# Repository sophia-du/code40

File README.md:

# code40
Pro-Micro compatible 40% ortholinear keyboard
- [Case Specifications](https://github.com/sophia-du/code40/blob/main/case/README.md)
- [PCB Specifications](https://github.com/sophia-du/code40/blob/main/pcb/README.md)
- [Firmware](https://github.com/sophia-du/code40/blob/main/qmk/README.md)
#

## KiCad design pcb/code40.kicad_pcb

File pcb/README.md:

# PCB Specifications
- Dimensions: 229 x 105 x 1.6 mm
- 2 layers, 1.6 mm thick, 1 oz copper
## Hardware
| Component | Amount |
|-----------|--------|
| Pro-Micro Compatible Microcontroller w/ Headers| 1 |
| 6 x 6 mm Push Button | 1 |
| 100 Ω Through-Hole Resistors | 2 |
| 5 mm Through-Hole LEDs | 2 |
| 1N4148 Diodes | 47 |
| Cherry MX Compatible Switches | 47 |
| 2u PCB Mounted Stabilizers | 1 |
## Assembly

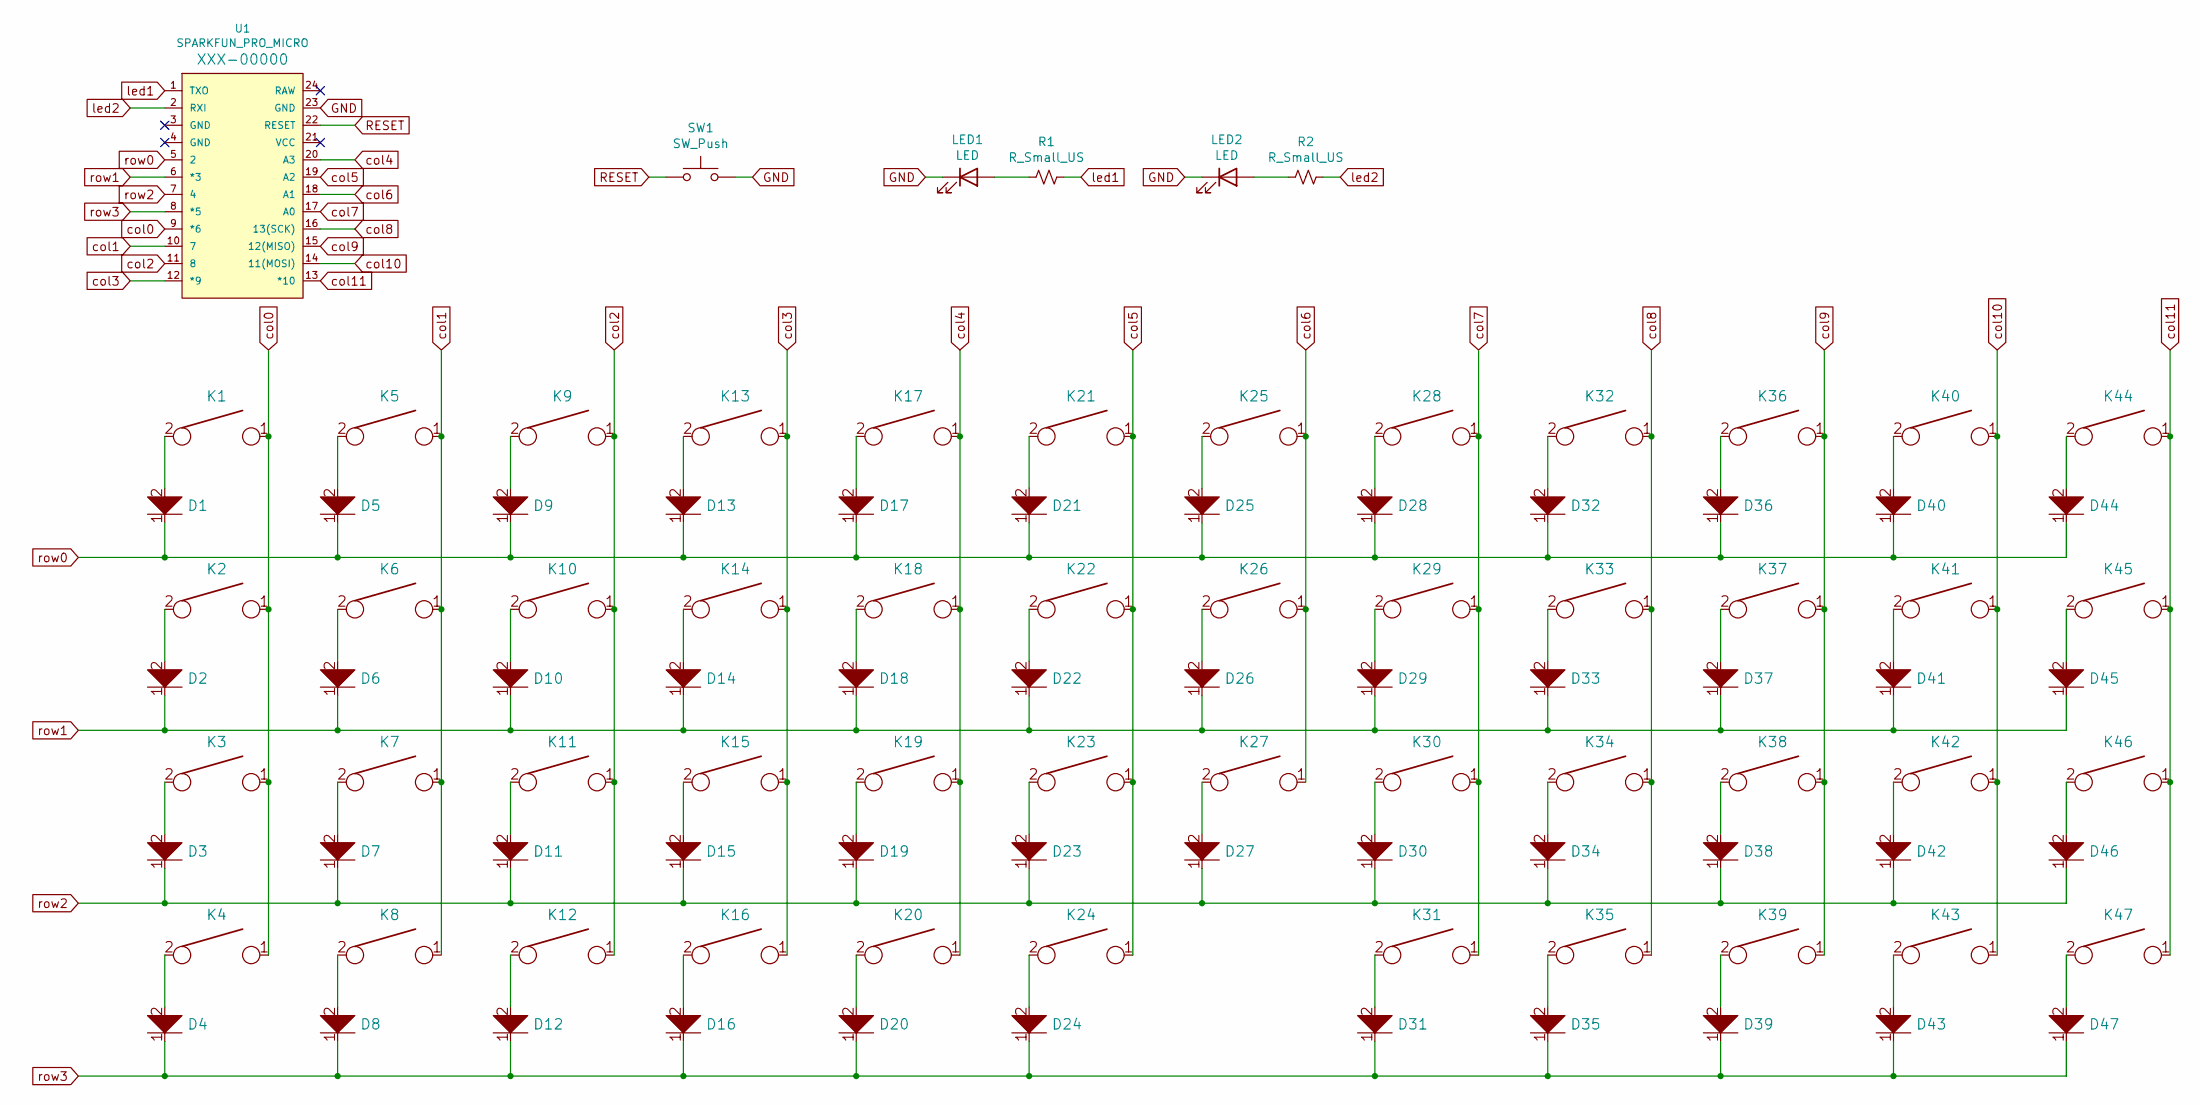
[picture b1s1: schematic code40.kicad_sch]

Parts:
D1, D2, D3, D4, D5, D6, D7, D8, D9, D10, D11, D12, D13, D14, D15, D16, D17, D18, D19, D20, D21, D22, D23, D24, D25, D26, D27, D28, D29, D30, D31, D32, D33, D34, D35, D36, D37, D38, D39, D40, D41, D42, D43, D44, D45, D46, D47: D; D_axial
K1, K2, K3, K4, K5, K6, K7, K8, K9, K10, K11, K12, K13, K14, K15, K16, K17, K18, K19, K20, K21, K22, K23, K25, K26, K27, K28, K29, K30, K31, K32, K33, K34, K35, K36, K37, K38, K39, K40, K41, K42, K43, K44, K45, K46, K47: KEYSW; SW_Cherry_MX_1.00u_PCB
K24: KEYSW; SW_Cherry_MX_2.00u_PCB
LED1, LED2: LED; LED_D5.0mm
R1, R2: R_Small_US; R_Axial_DIN0207_L6.3mm_D2.5mm_P10.16mm_Horizontal
SW1: SW_Push; SW_PUSH_6mm
U1: SPARKFUN_PRO_MICRO

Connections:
GND: LED1.1 (K), LED2.1 (K), SW1.2, U1.23 (GND)
unnamed: D1.2, K1.2
unnamed: D2.2, K2.2
unnamed: D3.2, K3.2
unnamed: D4.2, K4.2
unnamed: D5.2, K5.2
unnamed: D6.2, K6.2
unnamed: D7.2, K7.2
unnamed: D8.2, K8.2
unnamed: D9.2, K9.2
unnamed: D10.2, K10.2
unnamed: D11.2, K11.2
unnamed: D12.2, K12.2
unnamed: D13.2, K13.2
unnamed: D14.2, K14.2
unnamed: D15.2, K15.2
unnamed: D16.2, K16.2
unnamed: D17.2, K17.2
unnamed: D18.2, K18.2
unnamed: D19.2, K19.2
unnamed: D20.2, K20.2
unnamed: D21.2, K21.2
unnamed: D22.2, K22.2
unnamed: D23.2, K23.2
unnamed: D24.2, K24.2
unnamed: D25.2, K25.2
unnamed: D26.2, K26.2
unnamed: D27.2, K27.2
unnamed: D28.2, K28.2
unnamed: D29.2, K29.2
unnamed: D30.2, K30.2
unnamed: D31.2, K31.2
unnamed: D32.2, K32.2
unnamed: D33.2, K33.2
unnamed: D34.2, K34.2
unnamed: D35.2, K35.2
unnamed: D36.2, K36.2
unnamed: D37.2, K37.2
unnamed: D38.2, K38.2
unnamed: D39.2, K39.2
unnamed: D40.2, K40.2
unnamed: D41.2, K41.2
unnamed: D42.2, K42.2
unnamed: D43.2, K43.2
unnamed: D44.2, K44.2
unnamed: D45.2, K45.2
unnamed: D46.2, K46.2
unnamed: D47.2, K47.2
unnamed: LED1.2 (A), R1.2
unnamed: LED2.2 (A), R2.2
RESET: SW1.1, U1.22 (RESET)
col0: K1.1, K2.1, K3.1, K4.1, U1.9 (*6)
col1: K5.1, K6.1, K7.1, K8.1, U1.10 (7)
col2: K9.1, K10.1, K11.1, K12.1, U1.11 (8)
col3: K13.1, K14.1, K15.1, K16.1, U1.12 (*9)
col4: K17.1, K18.1, K19.1, K20.1, U1.20 (A3)
col5: K21.1, K22.1, K23.1, K24.1, U1.19 (A2)
col6: K25.1, K26.1, K27.1, U1.18 (A1)
col7: K28.1, K29.1, K30.1, K31.1, U1.17 (A0)
col8: K32.1, K33.1, K34.1, K35.1, U1.16 (13(SCK))
col9: K36.1, K37.1, K38.1, K39.1, U1.15 (12(MISO))
col10: K40.1, K41.1, K42.1, K43.1, U1.14 (11(MOSI))
col11: K44.1, K45.1, K46.1, K47.1, U1.13 (*10)
led1: R1.1, U1.1 (TXO)
led2: R2.1, U1.2 (RXI)
row0: D1.1, D5.1, D9.1, D13.1, D17.1, D21.1, D25.1, D28.1, D32.1, D36.1, D40.1, D44.1, U1.5 (2)
row1: D2.1, D6.1, D10.1, D14.1, D18.1, D22.1, D26.1, D29.1, D33.1, D37.1, D41.1, D45.1, U1.6 (*3)
row2: D3.1, D7.1, D11.1, D15.1, D19.1, D23.1, D27.1, D30.1, D34.1, D38.1, D42.1, D46.1, U1.7 (4)
row3: D4.1, D8.1, D12.1, D16.1, D20.1, D24.1, D31.1, D35.1, D39.1, D43.1, D47.1, U1.8 (*5)

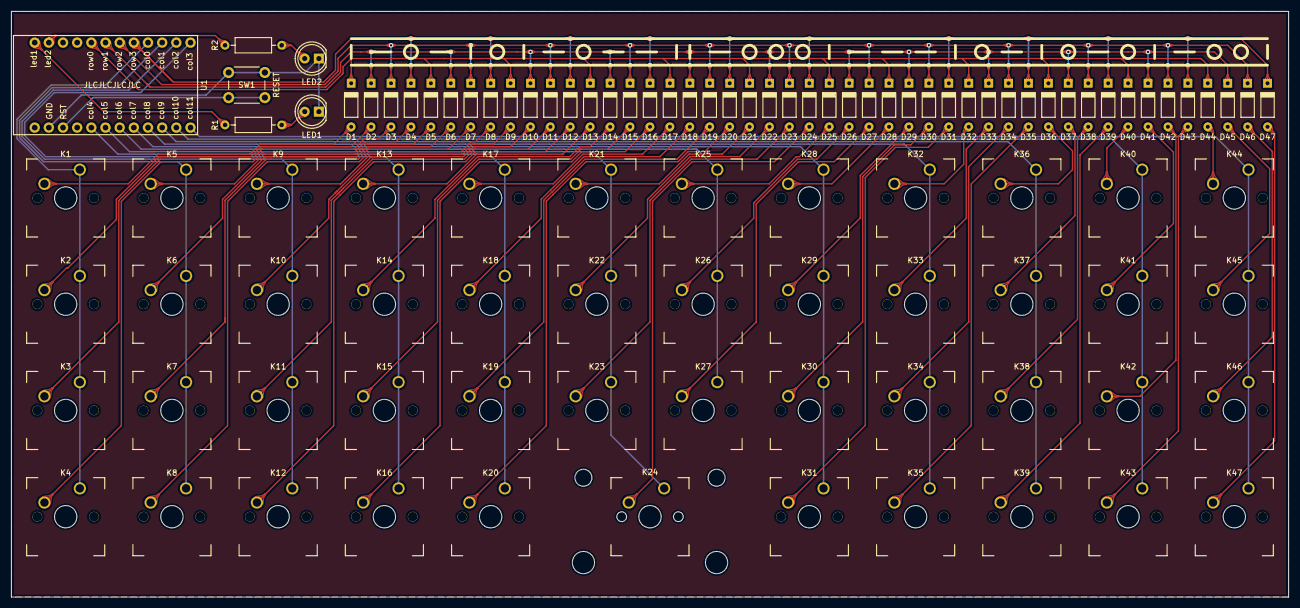
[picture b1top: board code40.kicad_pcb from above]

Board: 2 copper layers, 229.0 x 105.0 mm, 101 parts (1 on the bottom side), 69 nets.

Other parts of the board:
ST1: Stabilizer_Cherry_MX_2.00u

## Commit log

2022-10-23 test
2023-03-10 Rename case.md to README.md
2023-03-10 Rename pcb.md to README.md
2023-03-10 Rename qmk.md to README.md
2024-02-22 new kicad version
